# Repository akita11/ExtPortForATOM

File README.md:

# ExtPortForATOM

M5stackのATOMシリーズ ([Lite](https://www.switch-science.com/products/6262) / [Matrix](https://www.switch-science.com/products/6260)に3つのGroveポートを拡張します。Groveポートへの給電はATOMから、またはUSB Type-Cコネクタからを選択できます。

※M5Stack純正の[ATOM PortABC](https://www.switch-science.com/products/9198)とピン配置・コネクタの色は同一ですが、Portの名称が異なります(本品=B/C/D、ATOM PortABC=A/B/C)

## 使い方

ATOMを上図のように取り付けて使います。

GroveポートのVDD(+5V)への給電は、ボード上のショートピンで切り替えることができます。

- ”ATOM"側 : ATOMの+5V端子から給電（デフォルト）
- ”USB"側 : USB Type-C端子から給電（別途、USB ACアダプタやモバイルバッテリ等から給電してください）

## ピン配置

各ポートはATOMの以下のIOピンに接続されています。UIFlowからも利用可能となる予定です。

- PortB（赤色） : IO21/IO25/VDD/GND
- PortC（黒色） : IO33/IO23/VDD/GND
- PortD（青色） : IO19/IO22/VDD/GND

※ATOM-S3の場合は以下のようになります。

- PortB（赤色） : IO39/IO38/VDD/GND
- PortC（黒色） : IO8/IO7/VDD/GND
- PortD（青色） : IO6/IO5/VDD/GND

※初期ロットでは裏面シルクに間違いがあります。PortBとPortCの表記が逆になっていますのでご注意ください。（コネクタの色で各Portの名称を確認してください）

## Author

Junichi Akita (akita@ifdl.jp, @akita11)

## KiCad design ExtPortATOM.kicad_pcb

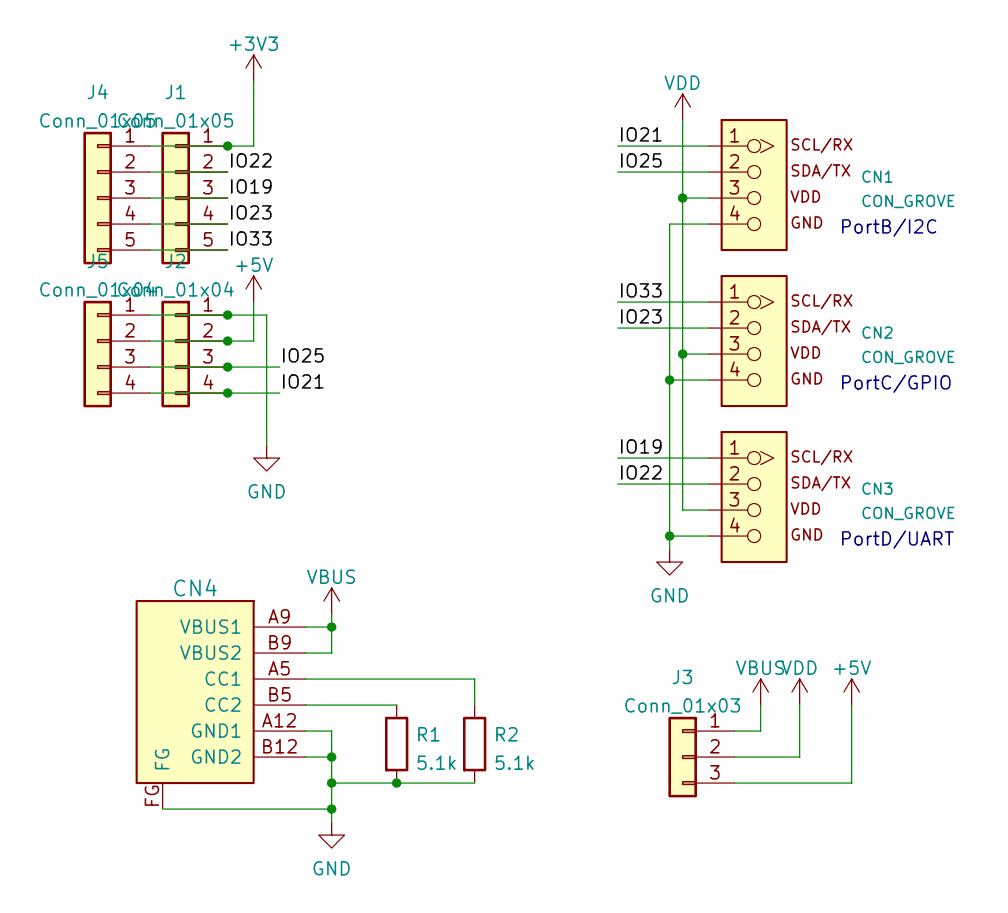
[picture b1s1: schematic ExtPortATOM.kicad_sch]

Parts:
CN1, CN2, CN3: CON_GROVE; CON_GROVE_H
CN4: CON_USB-C-6; USB-C_6P
J1, J4: Conn_01x05; PinHeader_1x05_P2.54mm_Vertical
J2, J5: Conn_01x04; PinHeader_1x04_P2.54mm_Vertical
J3: Conn_01x03; PinHeader_1x03_P2.54mm_Vertical
R1, R2: 5.1k; R_0603_1608Metric

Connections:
+3V3: J1.1, J4.1
+5V: J2.2, J3.3, J5.2
/IO19: CN3.1, J1.3, J4.3
/IO21: CN1.1, J2.4, J5.4
/IO22: CN3.2, J1.2, J4.2
/IO23: CN2.2, J1.4, J4.4
/IO25: CN1.2, J2.3, J5.3
/IO33: CN2.1, J1.5, J4.5
GND: CN1.4, CN2.4, CN3.4, CN4.A12 (GND1), CN4.B12 (GND2), CN4.FG, J2.1, J5.1, R1.2, R2.2
unnamed: CN4.A5 (CC1), R2.1
unnamed: CN4.B5 (CC2), R1.1
VBUS: CN4.A9 (VBUS1), CN4.B9 (VBUS2), J3.1
VDD: CN1.3, CN2.3, CN3.3, J3.2

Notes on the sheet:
PortD/UART
PortB/I2C
PortC/GPIO

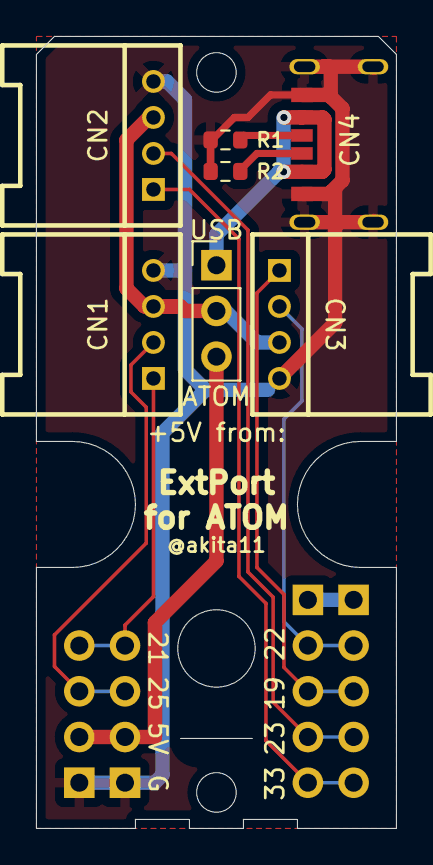
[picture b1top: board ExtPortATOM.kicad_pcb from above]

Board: 2 copper layers, 20.0 x 44.0 mm, 11 parts (0 on the bottom side), 13 nets.

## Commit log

2022-10-30 typo fix
2022-10-30 add board data
2024-07-19 pin assign for ATOM-S3
2024-07-28 for ATOM-S3
